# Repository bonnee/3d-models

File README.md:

# 3D Models

Collection of self-designed 3D models made for FDM 3D-printing.

## Usage
The included makefile takes care of building this file. It can also generate STL models from [SolveSpace](https://solvespace.com) and [FreeCAD](https://www.freecadweb.org/) project sources.

### Warning
FCStd models are incompatible with upstream FreeCAD. I created them using realthunder's [LinkStage3 branch](https://github.com/realthunder/FreeCAD/tree/LinkStage3) of FreeCAD.

- `make` to generate all
- `make freecad` to export FreeCAD projects to STL meshes
- `make solvespace` to export SolveSpace projects to STL meshes
- `make upload` to upload selected models to Thingiverse. Needs an `upload.json` file like [this one](precision_screwdriver_v2/upload.json).
- `make clean` to clean all.

## Table of contents
TBD

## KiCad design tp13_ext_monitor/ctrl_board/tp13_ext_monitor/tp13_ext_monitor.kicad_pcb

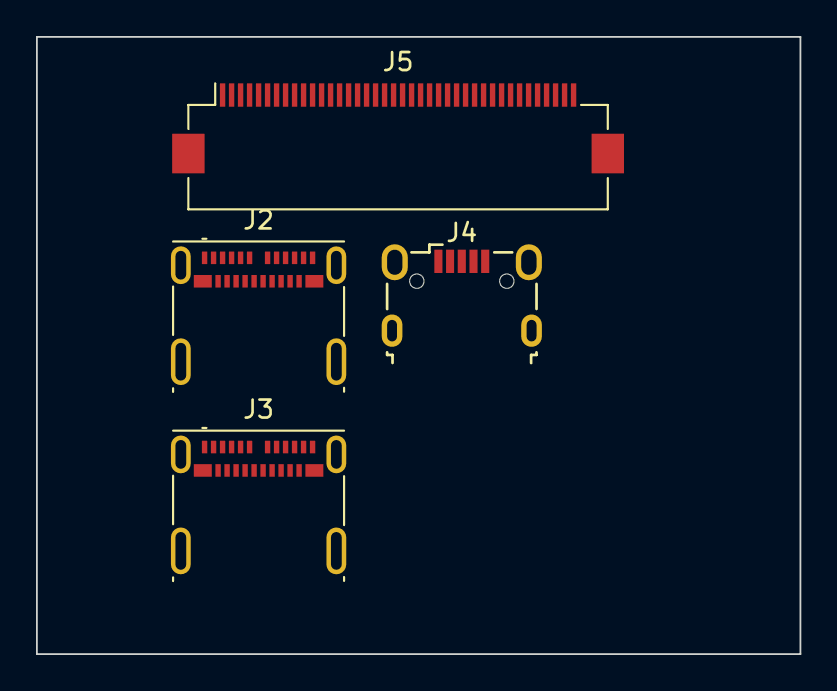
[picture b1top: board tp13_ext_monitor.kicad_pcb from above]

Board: 2 copper layers, 42.4 x 34.3 mm, 4 parts (0 on the bottom side), 4 nets, no tracks yet.

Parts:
J2, J3: USB_C_Receptacle; USB_C_Receptacle_Molex_105450-0101
J4: USB_B_Micro; USB_Micro-B_Wuerth_629105150521
J5: Conn_01x40_Socket; Hirose_FH12-40S-0.5SH_1x40-1MP_P0.50mm_Horizontal

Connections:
unnamed: J2.A1 (GND), J2.A12 (GND), J2.B1 (GND), J2.B12 (GND)
unnamed: J2.A4 (VBUS), J2.A9 (VBUS), J2.B4 (VBUS), J2.B9 (VBUS)
unnamed: J3.A1 (GND), J3.A12 (GND), J3.B1 (GND), J3.B12 (GND)
unnamed: J3.A4 (VBUS), J3.A9 (VBUS), J3.B4 (VBUS), J3.B9 (VBUS)

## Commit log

2020-03-11 Add lamp_bracket
2020-03-11 Add thingiverse link
2020-03-15 Add curtain holder
2020-03-15 Add tool_holder
2020-03-15 Update readme and rename curtain_holder
2020-03-15 Fix tool holder
2020-03-20 Add toorx mount
2020-03-30 Update toorx mount
2020-03-30 Add ender 5 filament sensor holder
2020-04-22 Streamline ender 5 filament sensor holder
2020-04-22 Add dishwasher salt cap tool
2020-04-22 Fix dishwasher cap tool
2020-04-22 Fix dishwasher tool tolerances
2020-05-08 Add chromebook feet
2020-05-08 Add bafang cap
2020-05-08 Update bafang cap tolerances
2020-05-21 Improve bafang cap printability
2020-05-21 Add panel-wall-mount
2020-06-01 Add drip catcher
2020-06-01 Redesign drip catcher
2020-06-02 Add bored holes to drip catcher
2020-06-09 Add precision screwdriver
2020-06-10 Finalize precision screwdriver
2020-06-10 Reorganize folders and update README
2020-09-06 Add Samsung monitor risers
2020-09-23 Add aim65-keyboard
2020-11-17 Update aim65
2020-11-17 Add yeelight headphone holder
2021-01-12 Add AM2302 ESP-01 enclosure
2021-01-12 Add Hi-Tek/Stackpole keycap to Cherry MX adapter
2021-01-12 hi-tek_mx_adapter: Adjust stem tolerance
2021-01-24 hi-tek_mx_adapter: Add images
2021-01-24 Add readme generation with makefile
2021-01-24 Fix readme link
2021-01-24 Add automatic solvespace stl export
2021-01-24 Add github action for readme
2021-01-24 {chore: autopublish 2021-01-24T16:06:59Z}
2021-01-24 Update workflow commit config
2021-01-24 Add IKEA SKADIS stuff
2021-01-24 Reduce chord tolerance on export
2021-01-24 Add tablet_treadmill
2021-01-24 Add tektronix TDS 220 power button
2021-01-24 Update makefile
2021-01-24 Add READMEs
2021-01-27 Add Logitech Z407 back plate
2021-01-27 logi_z407: update readme
2021-01-27 logi_z407: update model
2021-01-28 make: add freecad build
2021-01-28 {Build FreeCAD files}
2021-01-28 Make: polish build system
2021-01-28 readme: update readme header
2021-01-29 make: add solvespace dockerfile, remove freecad dockerfile
2021-01-29 Build STL meshes
2021-01-29 Split automatic commits
2021-01-29 Add ikea_drawer_organizers
2021-01-29 Build README.md
2021-01-29 Add palmrest_monitor_holder
2021-01-29 Build SolveSpace projects
2021-01-29 hi-tek_mx_adapter: update model
2021-01-29 Build FreeCAD projects
2021-01-29 Add IKEA dagotto antislip
2021-01-29 ikea_dagotto: Update model
2021-02-01 skadis_box_shelf: Initial commit
2021-02-01 skadis_box_shelf: Thicken base, invert hooks
2021-02-07 Remove STL files
2021-02-07 make: Update workflow for new gitignore
2021-02-07 make: fix workflow
2021-02-07 make: push after every build
2021-02-07 make: workaround failures
2021-02-07 Add LICENSE
2021-02-24 litophane_candle: initial commit
2021-03-01 litophane_candle: adjust size
2021-03-13 super struts: initial commit
2021-03-15 lithophane_candle: fix readme
2021-03-23 shelly: initial commit
2021-03-23 table_join_clamp: initial commit
2021-03-23 shelly_box: initial commit
2021-03-23 MRX-108_knobs: initial commit
2021-04-03 hi-tek_mx_adapter: Add step file
2021-04-03 table_hook: initial commit
2021-04-05 precision_screwdriver_v2: initial commit
2021-04-05 update exports
2021-04-15 precision_screwdriver_v2: improve tolerances
2021-04-15 table_hook: angle hook up to contrast bending
2021-04-16 scr_4000w: initial commit
2021-04-16 W3230_thermostat: initial commit
2021-04-16 update actions
2021-04-18 blackmagic_pill: initial commit
2021-04-18 blackmagic_pill: don't roll your own connector
2021-06-12 precision_screwdriver_v2: finalize design. Shorten handle
2021-10-01 ender5: add switch panel
2021-10-01 3018: add power supply holder
2021-10-04 3018: add emergency button
2021-10-07 makefile: update FreeCAD filenames to reflect FreeCAD's naming scheme
2021-10-07 3018: move all projects to dedicated directory
2021-10-07 precision_screwdriver_v2: Reduce handle file size
2021-10-07 3018: add missing enclosure files
2021-10-19 make: overhaul freecad build system. Create upload scripts
2021-10-24 500: add Fiat 500 headlight cover
2021-11-17 joystick: initial concept
2021-11-18 Add Table of Contents template for README.md
2021-12-05 air raid siren: Initial commit
2021-12-12 tesla_umc_holder: initial commit
2022-01-16 Rearrange folders
2022-01-16 Update thingiverse_upload script
2022-01-16 A miracle has happened and the makefile works as I want.
2022-01-16 Disable readme generation
2022-01-17 Wire up automatic thingiverse upload
2022-01-17 3018: add upload.json to enclosure
2022-01-17 Add various upload.json files
2022-01-17 Improve logging of thingiverse upload script
2022-01-17 precision_screwdriver_v2: Update files
2022-01-17 yeelight_bracket: add side versions to thingiverse
2022-01-18 3018_enclosure: add fillet to top chamfer
2022-01-18 3018_enclosure: update file names
2022-01-30 naming fixes
2022-01-30 Add upload.json for 3018
2022-02-02 dps5015: initial commit
2022-02-03 dps5015: add centrifugal fan duct
2022-02-04 dps5015: change fan duct for axial fan
2022-02-04 dps5015: Add mounting hole to fan duct
2022-02-04 dps5015: Fix front panel. Add stl models
2022-02-05 dps5015: Add USB port on front panel
2022-02-08 dps5015: add rubber foot models
2022-02-08 dps5015: add sloped rubber foot
2022-02-08 dps5015: update panels
2022-02-24 Remake fan duct
2022-06-05 Update precision screwdriver to better handle change in parameters
2022-06-05 Push correct handle stl file for precision screwdriver v2
2022-06-08 Refactor magnet insert slot
2022-06-08 Fix number of tip holes
2022-06-09 Minor fillet and chamfer tweaks
2022-06-22 precision_screwdriver_v2: greatly simplify magnet holder. No need for weird fillets and chamfers anymore
2022-06-22 precision_screwdriver_v2: add step file to thingiverse
2022-06-26 Fix bit slot interference
2022-06-26 Increase parametricity
2022-06-26 Update files
2022-06-26 precision_screwdriver_v2: Fix number of canals
2022-08-02 dps5015: Overhaul front and rear panels for DC input
2022-08-02 precision_screwdriver_v2: Increase bit canals to 9. Now it fits 18 bits!
2022-08-06 dps5015: Fix front and back panel legends
2022-08-24 joystick: update outer sheel design to be more ergonomic
2022-08-24 precision_screwdriver_v2: Revert to 16 bit design. Improve bit slots entrances
2022-08-27 air_raid_siren: Add v2 for different motor
2022-09-20 Add pd_to_banana
2023-01-22 Add hotel keychain
2026-01-16 bump
